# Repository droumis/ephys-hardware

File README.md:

# physiology

Components:
microdrive, dome, diode adapter, cone

>Recommended

>>vendors:
stratasys direct manufacturing,
fictiv (San Francisco),
Fathom (Oakland),
inception 3d (Fremont),

>>methods:
polyjet,
polyjet hd

>>materials:
veroblue,
verowhite,
veroclear,
verogrey,
amberclear

>Not Recommended
>>materials:
veroblack

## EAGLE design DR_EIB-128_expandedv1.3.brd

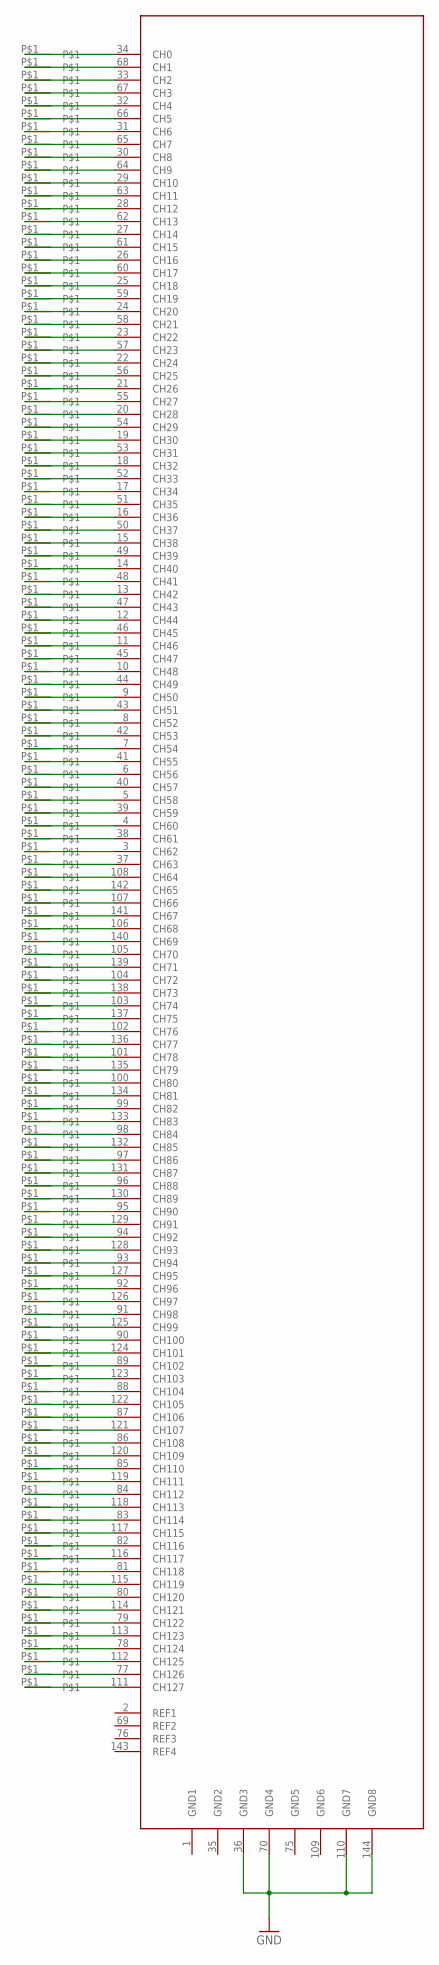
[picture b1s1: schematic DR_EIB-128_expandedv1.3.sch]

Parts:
H$0, H$1, H$2, H$3, H$4, H$5, H$6, H$7, H$8, H$9, H$10, H$11, H$12, H$13, H$14, H$15, H$16, H$17, H$18, H$19, H$20, H$21, H$22, H$23, H$24, H$25, H$26, H$27, H$28, H$29, H$30, H$31, H$32, H$33, H$34, H$35, H$36, H$37, H$38, H$39, H$40, H$41, H$42, H$43, H$44, H$45, H$46, H$47, H$48, H$49, H$50, H$51, H$52, H$53, H$54, H$55, H$56, H$57, H$58, H$59, H$60, H$61, H$62, H$63, H$64, H$65, H$66, H$67, H$68, H$69, H$70, H$71, H$72, H$73, H$74, H$75, H$76, H$77, H$78, H$79, H$80, H$81, H$82, H$83, H$84, H$85, H$86, H$87, H$88, H$89, H$90, H$91, H$92, H$93, H$94, H$95, H$96, H$97, H$98, H$99, H$100, H$101, H$102, H$103, H$104, H$105, H$106, H$107, H$108, H$109, H$110, H$111, H$112, H$113, H$114, H$115, H$116, H$117, H$118, H$119, H$120, H$121, H$122, H$123, H$124, H$125, H$126, H$127: TARRAYSHUTTLEHOLE
U$3: 128CH-MODULE

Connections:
GND: U$3.36 (GND3), U$3.70 (GND4), U$3.110 (GND7), U$3.144 (GND8)
GND1: U$3.1 (GND1)
GND2: U$3.35 (GND2)
GND5: U$3.75 (GND5)
GND6: U$3.109 (GND6)
unnamed: H$0.P$1, U$3.34 (CH0)
unnamed: H$1.P$1, U$3.68 (CH1)
unnamed: H$2.P$1, U$3.33 (CH2)
unnamed: H$3.P$1, U$3.67 (CH3)
unnamed: H$4.P$1, U$3.32 (CH4)
unnamed: H$5.P$1, U$3.66 (CH5)
unnamed: H$6.P$1, U$3.31 (CH6)
unnamed: H$7.P$1, U$3.65 (CH7)
unnamed: H$8.P$1, U$3.30 (CH8)
unnamed: H$9.P$1, U$3.64 (CH9)
unnamed: H$10.P$1, U$3.29 (CH10)
unnamed: H$11.P$1, U$3.63 (CH11)
unnamed: H$12.P$1, U$3.28 (CH12)
unnamed: H$13.P$1, U$3.62 (CH13)
unnamed: H$14.P$1, U$3.27 (CH14)
unnamed: H$15.P$1, U$3.61 (CH15)
unnamed: H$16.P$1, U$3.26 (CH16)
unnamed: H$17.P$1, U$3.60 (CH17)
unnamed: H$18.P$1, U$3.25 (CH18)
unnamed: H$19.P$1, U$3.59 (CH19)
unnamed: H$20.P$1, U$3.24 (CH20)
unnamed: H$21.P$1, U$3.58 (CH21)
unnamed: H$22.P$1, U$3.23 (CH22)
unnamed: H$23.P$1, U$3.57 (CH23)
unnamed: H$24.P$1, U$3.22 (CH24)
unnamed: H$25.P$1, U$3.56 (CH25)
unnamed: H$26.P$1, U$3.21 (CH26)
unnamed: H$27.P$1, U$3.55 (CH27)
unnamed: H$28.P$1, U$3.20 (CH28)
unnamed: H$29.P$1, U$3.54 (CH29)
unnamed: H$30.P$1, U$3.19 (CH30)
unnamed: H$31.P$1, U$3.53 (CH31)
unnamed: H$32.P$1, U$3.18 (CH32)
unnamed: H$33.P$1, U$3.52 (CH33)
unnamed: H$34.P$1, U$3.17 (CH34)
unnamed: H$35.P$1, U$3.51 (CH35)
unnamed: H$36.P$1, U$3.16 (CH36)
unnamed: H$37.P$1, U$3.50 (CH37)
unnamed: H$38.P$1, U$3.15 (CH38)
unnamed: H$39.P$1, U$3.49 (CH39)
unnamed: H$40.P$1, U$3.14 (CH40)
unnamed: H$41.P$1, U$3.48 (CH41)
unnamed: H$42.P$1, U$3.13 (CH42)
unnamed: H$43.P$1, U$3.47 (CH43)
unnamed: H$44.P$1, U$3.12 (CH44)
unnamed: H$45.P$1, U$3.46 (CH45)
unnamed: H$46.P$1, U$3.11 (CH46)
unnamed: H$47.P$1, U$3.45 (CH47)
unnamed: H$48.P$1, U$3.10 (CH48)
unnamed: H$49.P$1, U$3.44 (CH49)
unnamed: H$50.P$1, U$3.9 (CH50)
unnamed: H$51.P$1, U$3.43 (CH51)
unnamed: H$52.P$1, U$3.8 (CH52)
unnamed: H$53.P$1, U$3.42 (CH53)
unnamed: H$54.P$1, U$3.7 (CH54)
unnamed: H$55.P$1, U$3.41 (CH55)
unnamed: H$56.P$1, U$3.6 (CH56)
unnamed: H$57.P$1, U$3.40 (CH57)
unnamed: H$58.P$1, U$3.5 (CH58)
unnamed: H$59.P$1, U$3.39 (CH59)
unnamed: H$60.P$1, U$3.4 (CH60)
unnamed: H$61.P$1, U$3.38 (CH61)
unnamed: H$62.P$1, U$3.3 (CH62)
unnamed: H$63.P$1, U$3.37 (CH63)
unnamed: H$64.P$1, U$3.108 (CH64)
unnamed: H$65.P$1, U$3.142 (CH65)
unnamed: H$66.P$1, U$3.107 (CH66)
unnamed: H$67.P$1, U$3.141 (CH67)
unnamed: H$68.P$1, U$3.106 (CH68)
unnamed: H$69.P$1, U$3.140 (CH69)
unnamed: H$70.P$1, U$3.105 (CH70)
unnamed: H$71.P$1, U$3.139 (CH71)
unnamed: H$72.P$1, U$3.104 (CH72)
unnamed: H$73.P$1, U$3.138 (CH73)
unnamed: H$74.P$1, U$3.103 (CH74)
unnamed: H$75.P$1, U$3.137 (CH75)
unnamed: H$76.P$1, U$3.102 (CH76)
unnamed: H$77.P$1, U$3.136 (CH77)
unnamed: H$78.P$1, U$3.101 (CH78)
unnamed: H$79.P$1, U$3.135 (CH79)
unnamed: H$80.P$1, U$3.100 (CH80)
unnamed: H$81.P$1, U$3.134 (CH81)
unnamed: H$82.P$1, U$3.99 (CH82)
unnamed: H$83.P$1, U$3.133 (CH83)
unnamed: H$84.P$1, U$3.98 (CH84)
unnamed: H$85.P$1, U$3.132 (CH85)
unnamed: H$86.P$1, U$3.97 (CH86)
unnamed: H$87.P$1, U$3.131 (CH87)
unnamed: H$88.P$1, U$3.96 (CH88)
unnamed: H$89.P$1, U$3.130 (CH89)
unnamed: H$90.P$1, U$3.95 (CH90)
unnamed: H$91.P$1, U$3.129 (CH91)
unnamed: H$92.P$1, U$3.94 (CH92)
unnamed: H$93.P$1, U$3.128 (CH93)
unnamed: H$94.P$1, U$3.93 (CH94)
unnamed: H$95.P$1, U$3.127 (CH95)
unnamed: H$96.P$1, U$3.92 (CH96)
unnamed: H$97.P$1, U$3.126 (CH97)
unnamed: H$98.P$1, U$3.91 (CH98)
unnamed: H$99.P$1, U$3.125 (CH99)
unnamed: H$100.P$1, U$3.90 (CH100)
unnamed: H$101.P$1, U$3.124 (CH101)
unnamed: H$102.P$1, U$3.89 (CH102)
unnamed: H$103.P$1, U$3.123 (CH103)
unnamed: H$104.P$1, U$3.88 (CH104)
unnamed: H$105.P$1, U$3.122 (CH105)
unnamed: H$106.P$1, U$3.87 (CH106)
unnamed: H$107.P$1, U$3.121 (CH107)
unnamed: H$108.P$1, U$3.86 (CH108)
unnamed: H$109.P$1, U$3.120 (CH109)
unnamed: H$110.P$1, U$3.85 (CH110)
unnamed: H$111.P$1, U$3.119 (CH111)
unnamed: H$112.P$1, U$3.84 (CH112)
unnamed: H$113.P$1, U$3.118 (CH113)
unnamed: H$114.P$1, U$3.83 (CH114)
unnamed: H$115.P$1, U$3.117 (CH115)
unnamed: H$116.P$1, U$3.82 (CH116)
unnamed: H$117.P$1, U$3.116 (CH117)
unnamed: H$118.P$1, U$3.81 (CH118)
unnamed: H$119.P$1, U$3.115 (CH119)
unnamed: H$120.P$1, U$3.80 (CH120)
unnamed: H$121.P$1, U$3.114 (CH121)
unnamed: H$122.P$1, U$3.79 (CH122)
unnamed: H$123.P$1, U$3.113 (CH123)
unnamed: H$124.P$1, U$3.78 (CH124)
unnamed: H$125.P$1, U$3.112 (CH125)
unnamed: H$126.P$1, U$3.77 (CH126)
unnamed: H$127.P$1, U$3.111 (CH127)

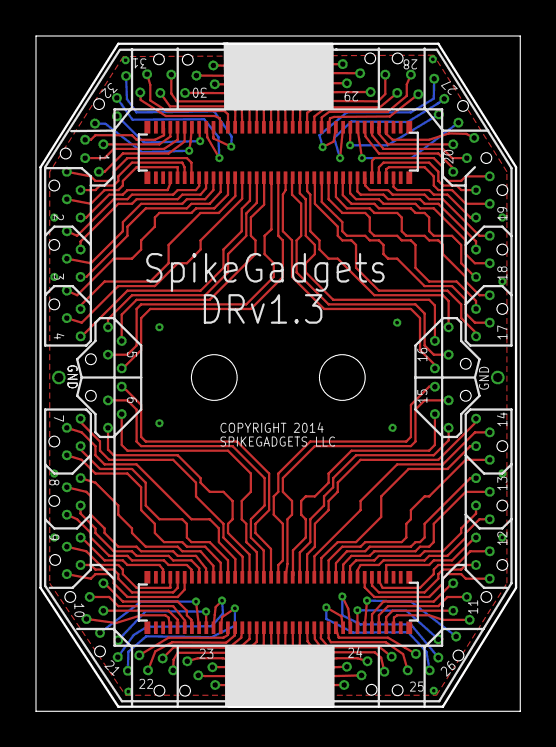
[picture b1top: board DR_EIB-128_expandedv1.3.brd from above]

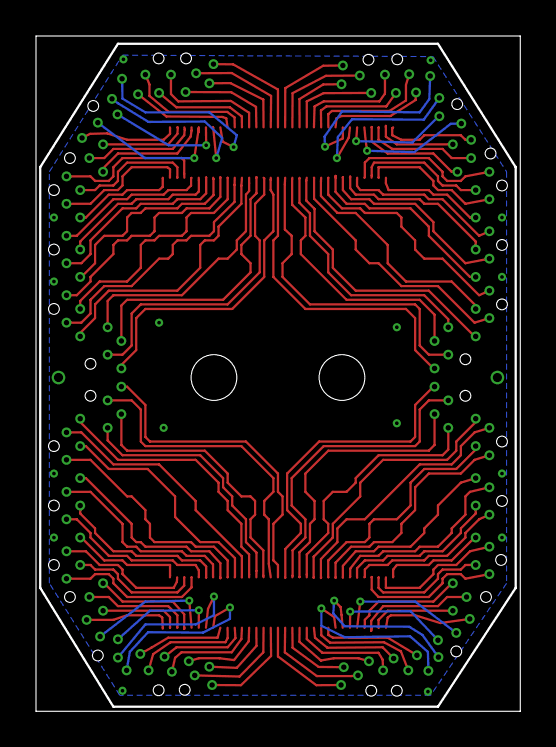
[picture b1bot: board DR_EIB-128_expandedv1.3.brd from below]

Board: 2 copper layers, 26.8 x 37.4 mm, 129 parts (59 on the bottom side), 129 nets.

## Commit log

2017-03-11 first
2017-03-11 adding drive v5 stl
2017-03-11 added current releases of drive cone dome diodes to repo
2017-03-11 cleaning up redundant drive file
2017-03-11 organizing into dirs
2017-03-11 adding shuttle and tooling notes
2017-03-12 Rename README.md to doc_orderInfo.md
2017-03-12 organizing docs
2017-03-12 reorganizing and adding new step shuttle file
2017-03-12 depricating v5 shuttle
2017-03-12 injection mold and 3d print shuttle parts
2017-03-12 fixing gitignore
2017-03-13 updating access to tooling notes
2017-03-13 added EIB v1.4 to repo
2017-03-13 testing
2017-03-13 cleaning
2017-04-05 pcb for reward well
2017-04-05 reward well pcb gerbers to repo

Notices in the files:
DR_EIB-128_expandedv1.3.brd:
COPYRIGHT 2014
